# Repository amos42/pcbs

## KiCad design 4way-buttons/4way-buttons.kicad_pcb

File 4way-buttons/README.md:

# Monitor Control Board

회로도

PCB 이미지

샘플 이미지

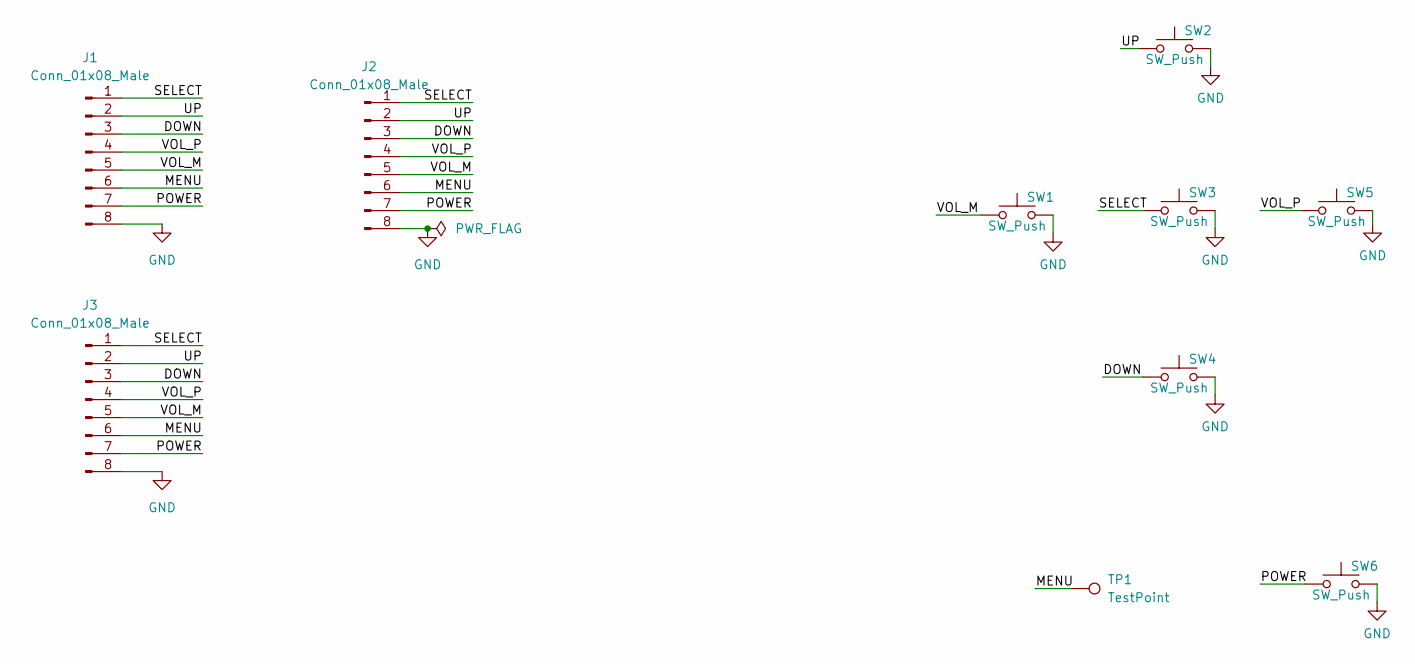
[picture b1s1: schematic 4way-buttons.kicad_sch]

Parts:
J1: Conn_01x08_Male; JST_GH_SM08B-GHS-TB_1x08-1MP_P1.25mm_Horizontal
J2: Conn_01x08_Male; PinHeader_1x08_P2.54mm_Vertical
J3: Conn_01x08_Male; JST_PH_S8B-PH-K_1x08_P2.00mm_Horizontal
SW1, SW2, SW3, SW4, SW5: SW_Push; SW_PUSH-12mm
SW6: SW_Push; SW_PUSH_6mm
TP1: TestPoint; TestPoint_Pad_D2.0mm

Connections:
/DOWN: J1.3, J2.3, J3.3, SW4.1
/MENU: J1.6, J2.6, J3.6, TP1.1
/POWER: J1.7, J2.7, J3.7, SW6.1
/SELECT: J1.1, J2.1, J3.1, SW3.1
/UP: J1.2, J2.2, J3.2, SW2.1
/VOL_M: J1.5, J2.5, J3.5, SW1.1
/VOL_P: J1.4, J2.4, J3.4, SW5.1
GND: J1.8, J2.8, J3.8, SW1.2, SW2.2, SW3.2, SW4.2, SW5.2, SW6.2

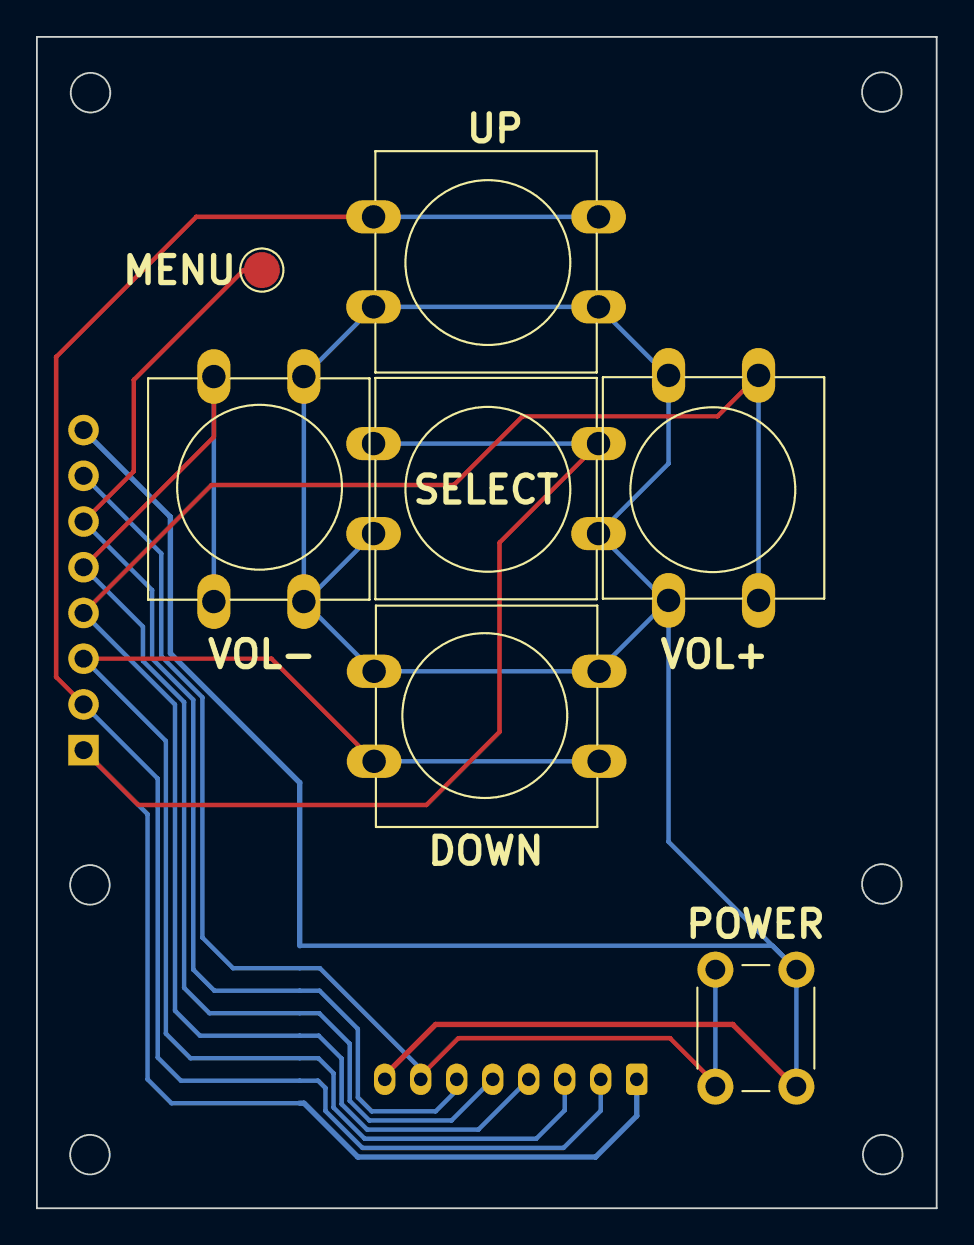
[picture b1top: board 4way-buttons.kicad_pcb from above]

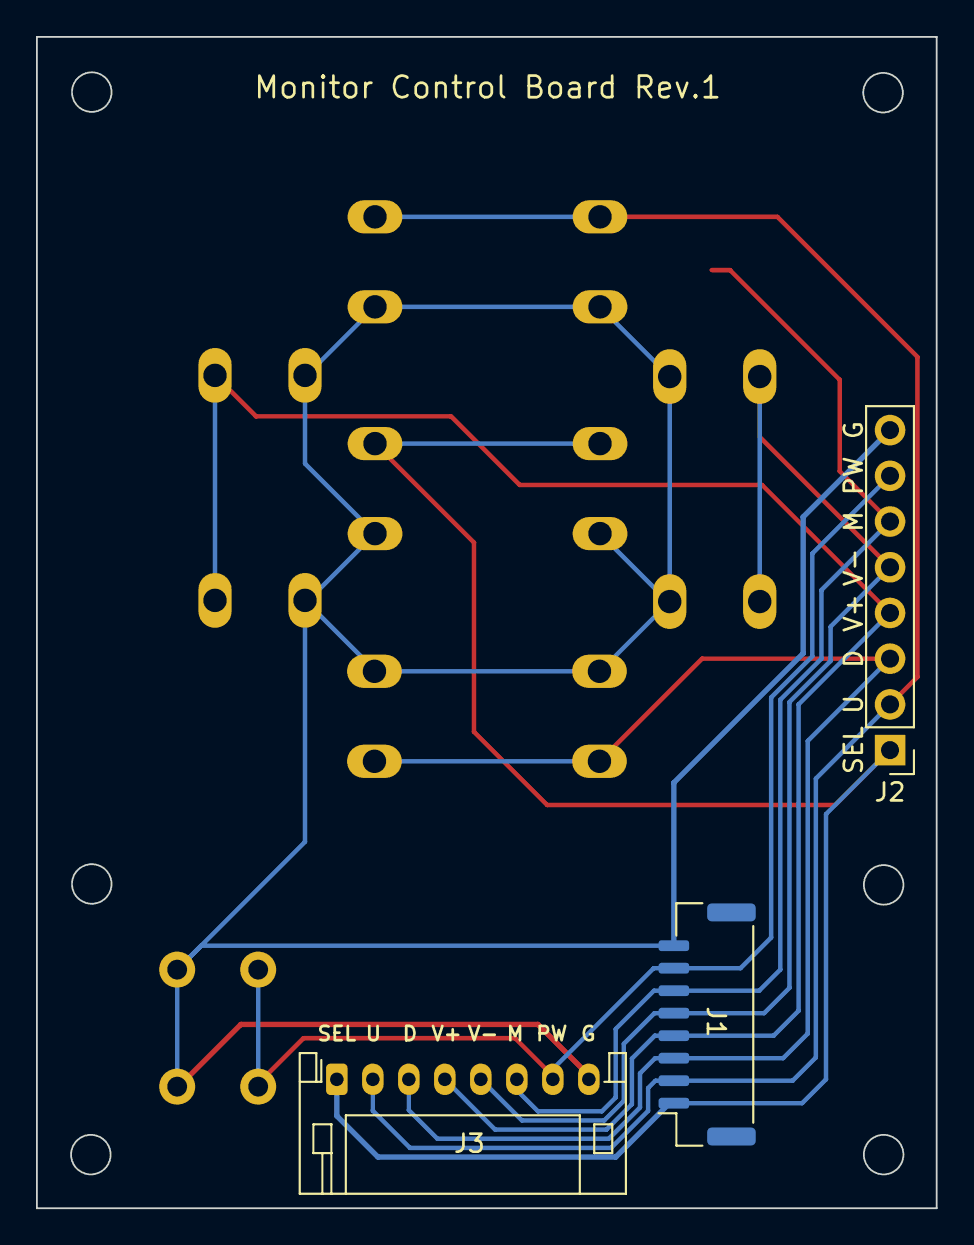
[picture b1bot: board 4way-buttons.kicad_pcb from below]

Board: 2 copper layers, 50.0 x 65.1 mm, 10 parts (3 on the bottom side), 8 nets.

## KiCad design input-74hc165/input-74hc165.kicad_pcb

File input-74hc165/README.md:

# 74HC165 입력 보드

회로도

PCB 이미지 앞면

PCB 이미지 뒷면

샘플 이미지

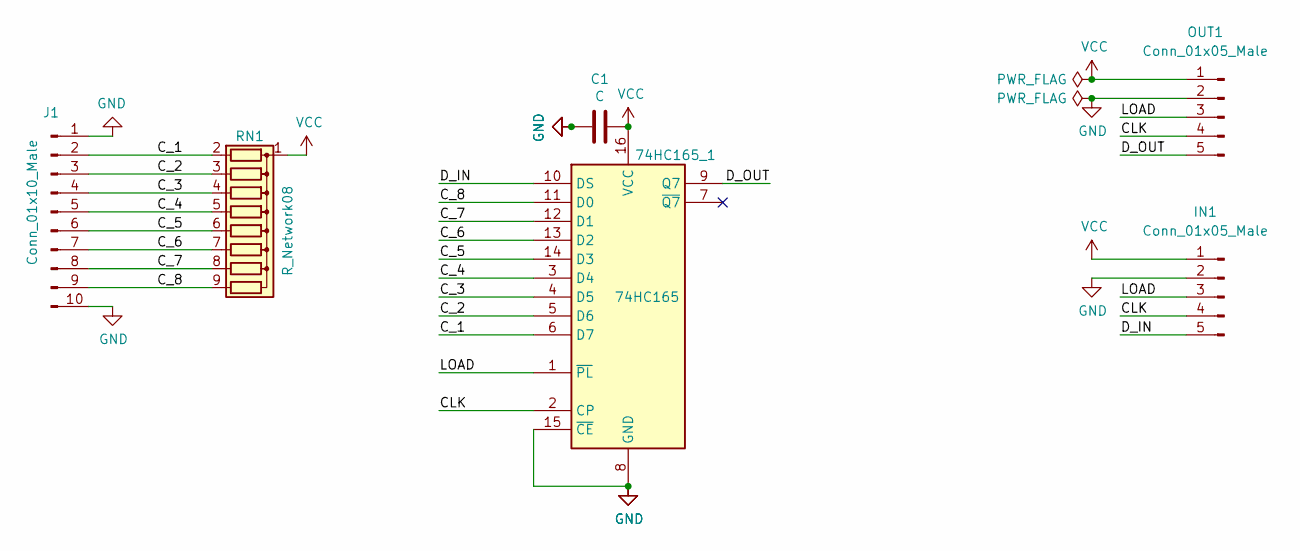
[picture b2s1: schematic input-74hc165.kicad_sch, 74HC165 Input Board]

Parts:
74HC165_1: 74HC165; DIP-16_W7.62mm
C1: C; C_Disc_D4.3mm_W1.9mm_P5.00mm
IN1: Conn_01x05_Male; PinHeader_1x05_P2.54mm_Vertical
J1: Conn_01x10_Male; PinHeader_1x10_P2.54mm_Vertical
OUT1: Conn_01x05_Male; PinHeader_1x05_P2.54mm_Vertical
RN1: R_Network08; R_Array_SIP9

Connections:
/CLK: 74HC165_1.2 (CP), IN1.4, OUT1.4
/C_1: 74HC165_1.6 (D7), J1.2, RN1.2 (R1)
/C_2: 74HC165_1.5 (D6), J1.3, RN1.3 (R2)
/C_3: 74HC165_1.4 (D5), J1.4, RN1.4 (R3)
/C_4: 74HC165_1.3 (D4), J1.5, RN1.5 (R4)
/C_5: 74HC165_1.14 (D3), J1.6, RN1.6 (R5)
/C_6: 74HC165_1.13 (D2), J1.7, RN1.7 (R6)
/C_7: 74HC165_1.12 (D1), J1.8, RN1.8 (R7)
/C_8: 74HC165_1.11 (D0), J1.9, RN1.9 (R8)
/D_IN: 74HC165_1.10 (DS), IN1.5
/D_OUT: 74HC165_1.9 (Q7), OUT1.5
/LOAD: 74HC165_1.1 (~PL), IN1.3, OUT1.3
GND: 74HC165_1.8 (GND), 74HC165_1.15 (~CE), C1.2, IN1.2, J1.1, J1.10, OUT1.2
VCC: 74HC165_1.16 (VCC), C1.1, IN1.1, OUT1.1, RN1.1 (common)

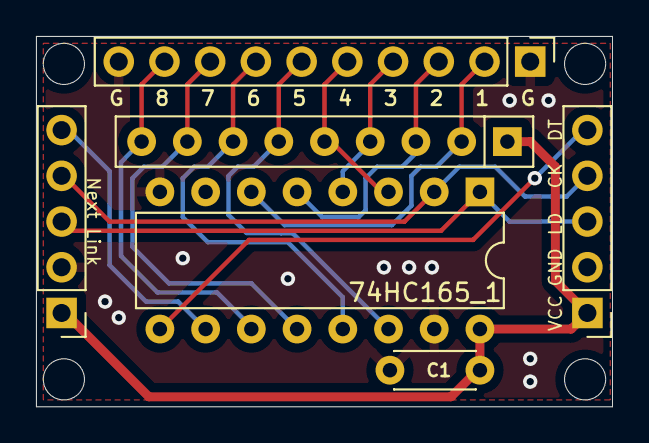
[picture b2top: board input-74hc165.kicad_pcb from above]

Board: 2 copper layers, 32.0 x 20.6 mm, 6 parts (0 on the bottom side), 14 nets.

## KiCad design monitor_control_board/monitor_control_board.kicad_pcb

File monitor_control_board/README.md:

# Monitor OSD Control Board

회로도

PCB 이미지

샘플 이미지

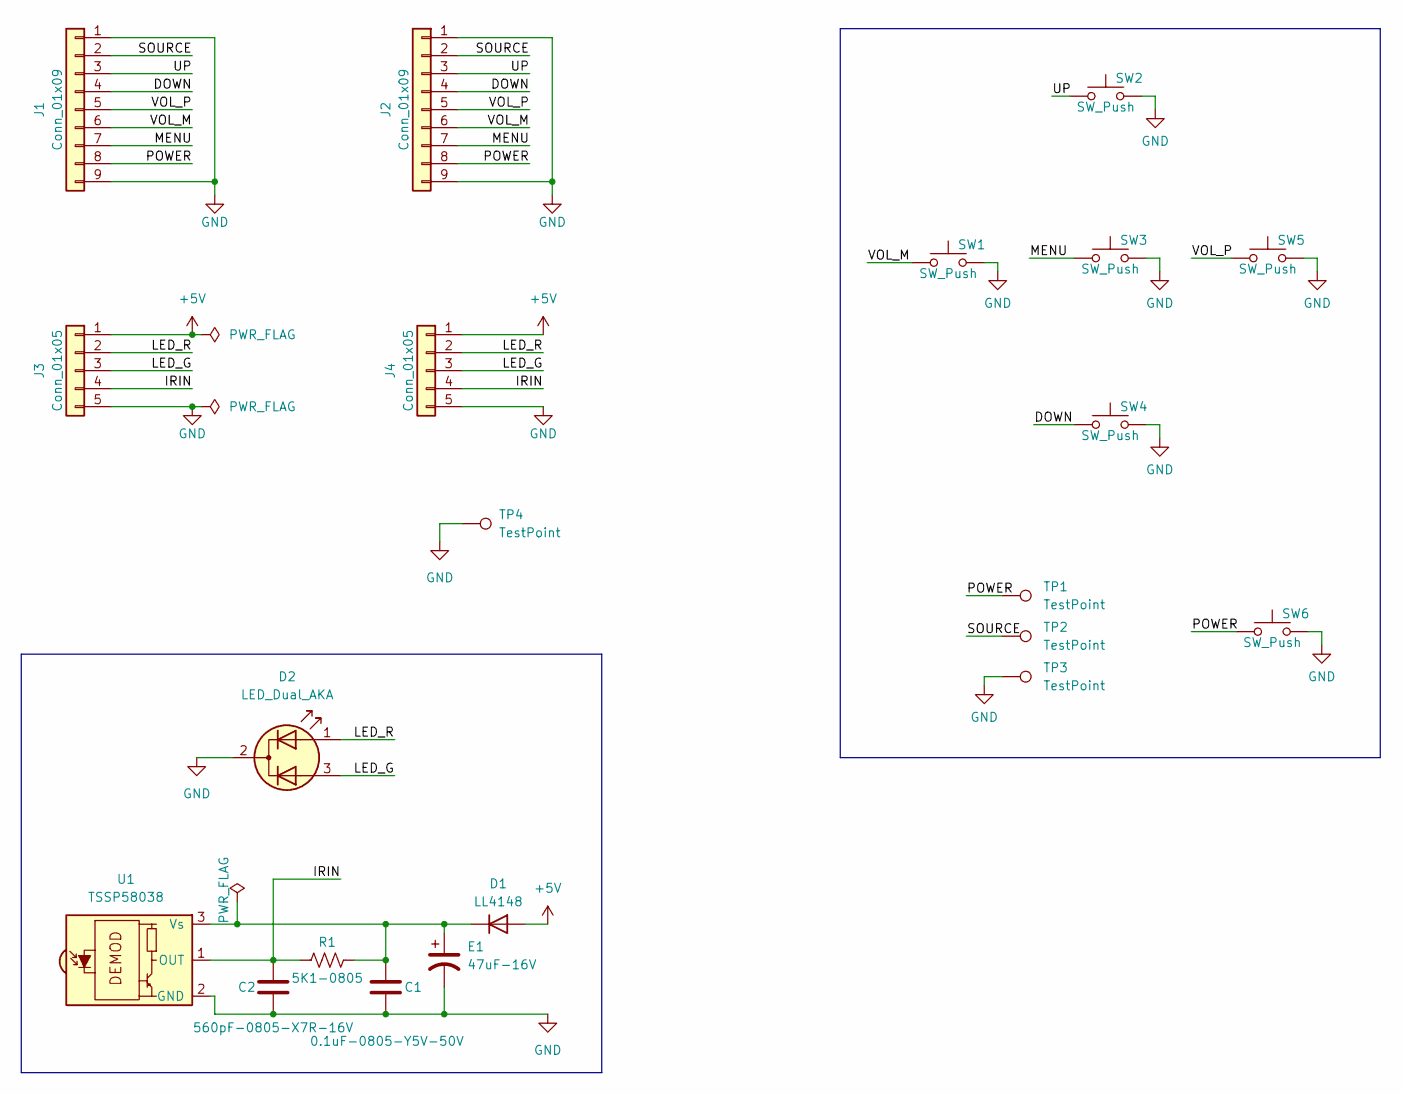
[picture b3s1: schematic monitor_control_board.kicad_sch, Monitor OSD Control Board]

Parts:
C1: 0.1uF-0805-Y5V-50V; C_0805_2012Metric_Pad1.18x1.45mm_HandSolder
C2: 560pF-0805-X7R-16V; C_0805_2012Metric_Pad1.18x1.45mm_HandSolder
D1: LL4148; D_MiniMELF
D2: LED_Dual_AKA; LED_D3.0mm-3
E1: 47uF-16V; CP_Elec_4x5.4
J1: Conn_01x09; PinHeader_1x09_P2.00mm_Vertical
J2: Conn_01x09; PinHeader_1x09_P2.54mm_Vertical
J3: Conn_01x05; PinHeader_1x05_P2.00mm_Vertical
J4: Conn_01x05; PinHeader_1x05_P2.54mm_Vertical
R1: 5K1-0805; R_0805_2012Metric_Pad1.20x1.40mm_HandSolder
SW1, SW2, SW3, SW4, SW5: SW_Push; SW_PUSH-12mm_Complex
SW6: SW_Push; SW_PUSH_6mm
TP1, TP2, TP3: TestPoint; TestPoint_THTPad_D1.5mm_Drill0.7mm
TP4: TestPoint; TestPoint_THTPad_D2.0mm_Drill1.0mm
U1: TSSP58038; Vishay_MINICAST-3Pin

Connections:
+5V: D1.2 (A), J3.1, J4.1
/DOWN: J1.4, J2.4, SW4.1
/IRIN: C2.1, J3.4, J4.4, R1.1, U1.1 (OUT)
/LED_G: D2.3 (A2), J3.3, J4.3
/LED_R: D2.1 (A1), J3.2, J4.2
/MENU: J1.7, J2.7, SW3.1
/POWER: J1.8, J2.8, SW6.1, TP1.1
/SOURCE: J1.2, J2.2, TP2.1
/UP: J1.3, J2.3, SW2.1
/VOL_M: J1.6, J2.6, SW1.1
/VOL_P: J1.5, J2.5, SW5.1
GND: C1.2, C2.2, D2.2 (K), E1.2, J1.1, J1.9, J2.1, J2.9, J3.5, J4.5, SW1.2, SW2.2, SW3.2, SW4.2, SW5.2, SW6.2, TP3.1, TP4.1, U1.2 (GND)
unnamed: C1.1, D1.1 (K), E1.1, R1.2, U1.3 (Vs)

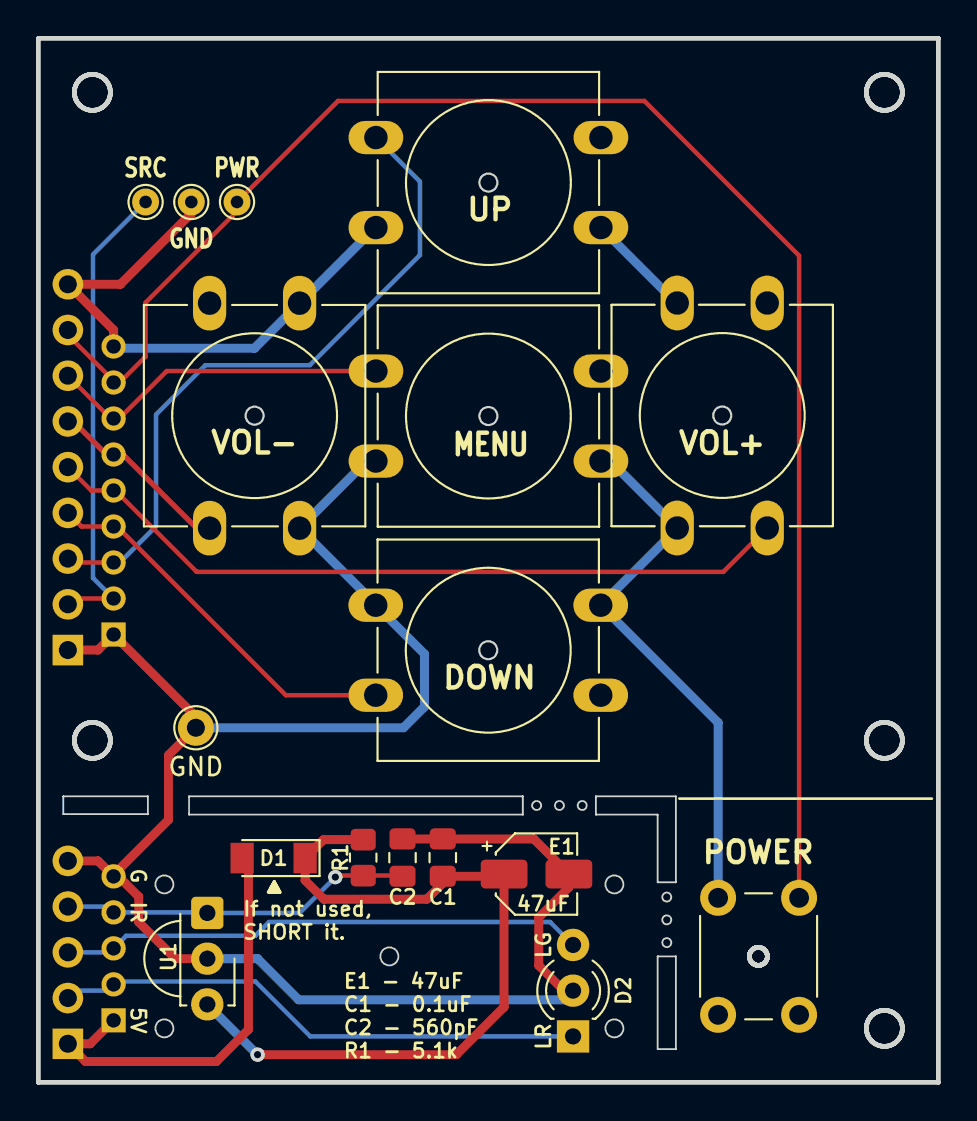
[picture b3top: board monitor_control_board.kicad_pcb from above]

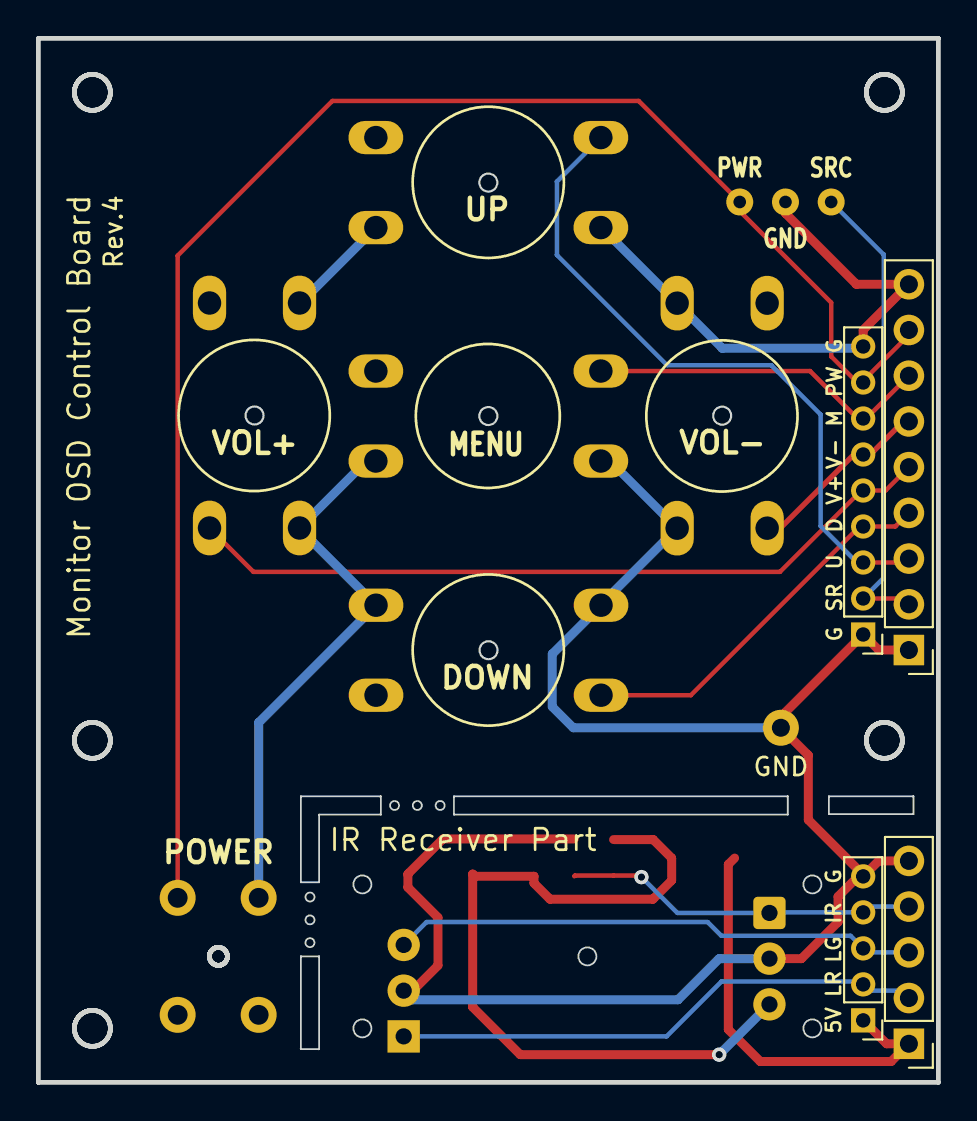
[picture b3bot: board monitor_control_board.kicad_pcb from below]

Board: 2 copper layers, 50.0 x 58.0 mm, 21 parts (4 on the bottom side), 13 nets.

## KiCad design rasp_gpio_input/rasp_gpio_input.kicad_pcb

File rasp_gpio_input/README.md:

# Raspberry Pie GPIO 입력 모듈

GPIO 보호 기능을 갖는 입력 모듈

---

## 회로도

## PCB

## BOM

| Designator | Package | Quantity | Designation |
|------------|---------|----------|-------------|
| R1~R13 | R_0805_2012Metric | 13 | 6.8K

## PCB 이미지

### 앞면

### 뒷면

## 샘플 이미지

## 점퍼 세팅

커넥터 중 J3는 일부 핀을 점퍼 세팅으로 변경이 가능하다.

* R* - 1-2 끊고 2-3 쇼트시, J3의 Right 핀이 GND로 쇼트
* ST* - 1-2 끊고 2-3 쇼트시, J3의 Start 핀이 GND로 쇼트
* SL* - 1-2 끊고 2-3 쇼트시, J3의 Select 핀이 GND로 쇼트
* HK* - 1-2 끊고 2-3 쇼트시, J3의 HotKey 핀이 GND로 쇼트

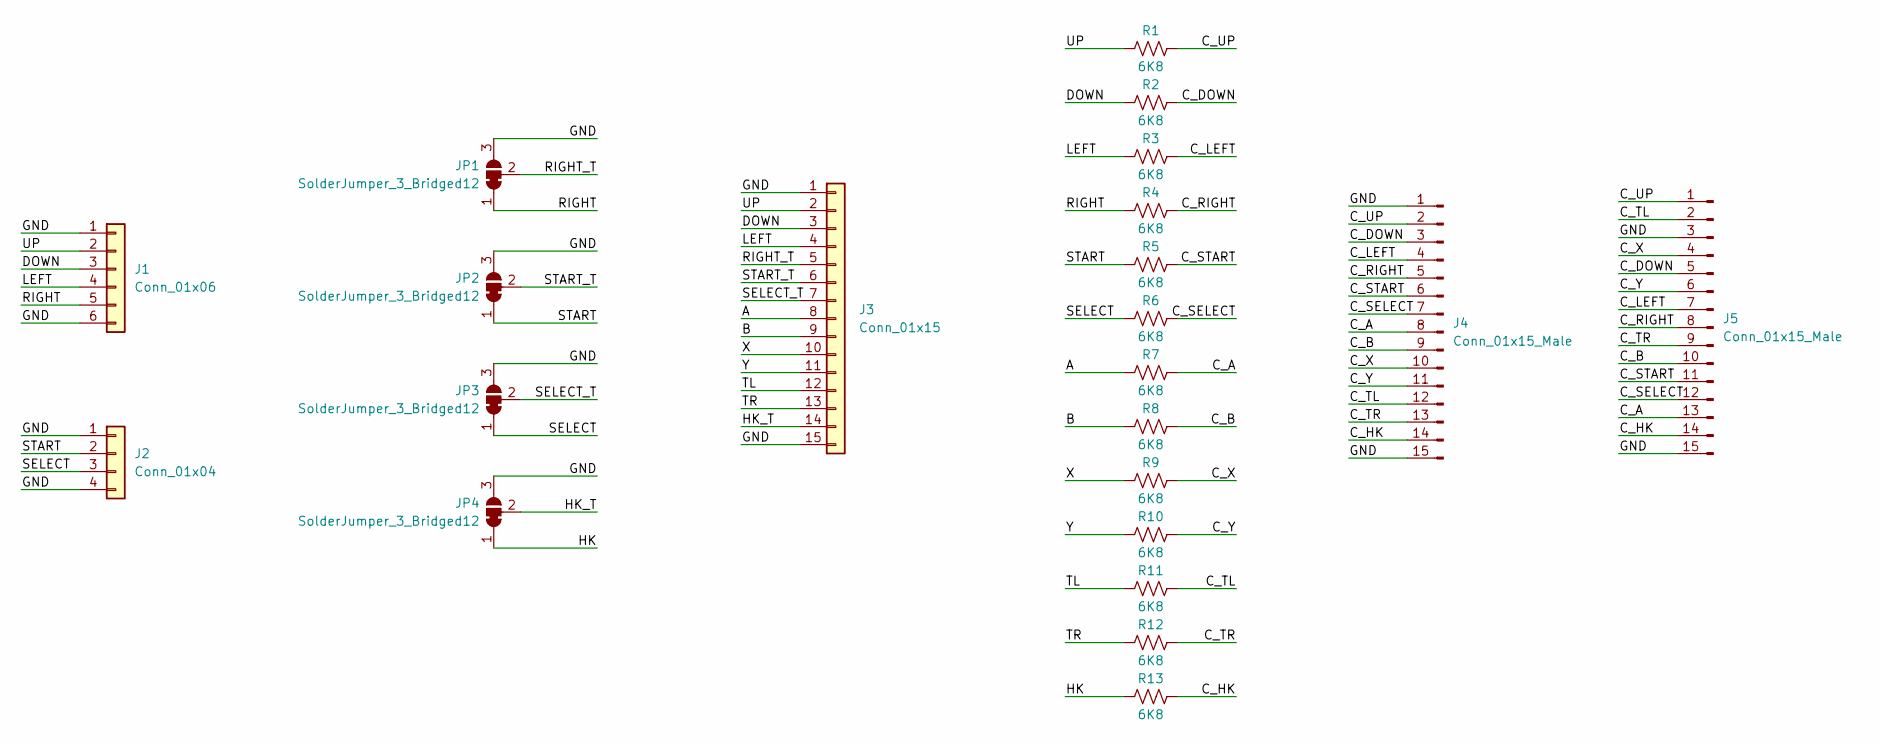
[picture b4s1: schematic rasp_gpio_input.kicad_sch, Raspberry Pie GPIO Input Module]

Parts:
J1: Conn_01x06; Molex_PicoBlade_53047-0610_1x06_P1.25mm_Vertical
J2: Conn_01x04; Molex_PicoBlade_53047-0410_1x04_P1.25mm_Vertical
J3: Conn_01x15; Molex_PicoBlade_53047-1510_1x15_P1.25mm_Vertical
J4, J5: Conn_01x15_Male; PinHeader_1x15_P2.54mm_Vertical
JP1, JP2, JP3, JP4: SolderJumper_3_Bridged12; SolderJumper-3_P1.3mm_Bridged12_Pad1.0x1.5mm
R1, R2, R3, R4, R5, R6, R7, R8, R9, R10, R11, R12, R13: 6K8; R_0805_2012Metric_Pad1.20x1.40mm_HandSolder

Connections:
/A: J3.8, R7.1
/B: J3.9, R8.1
/C_A: J4.8, J5.13, R7.2
/C_B: J4.9, J5.10, R8.2
/C_DOWN: J4.3, J5.5, R2.2
/C_HK: J4.14, J5.14, R13.2
/C_LEFT: J4.4, J5.7, R3.2
/C_RIGHT: J4.5, J5.8, R4.2
/C_SELECT: J4.7, J5.12, R6.2
/C_START: J4.6, J5.11, R5.2
/C_TL: J4.12, J5.2, R11.2
/C_TR: J4.13, J5.9, R12.2
/C_UP: J4.2, J5.1, R1.2
/C_X: J4.10, J5.4, R9.2
/C_Y: J4.11, J5.6, R10.2
/DOWN: J1.3, J3.3, R2.1
/GND: J1.1, J1.6, J2.1, J2.4, J3.1, J3.15, J4.1, J4.15, J5.3, J5.15, JP1.3 (B), JP2.3 (B), JP3.3 (B), JP4.3 (B)
/HK: JP4.1 (A), R13.1
/HK_T: J3.14, JP4.2 (C)
/LEFT: J1.4, J3.4, R3.1
/RIGHT: J1.5, JP1.1 (A), R4.1
/RIGHT_T: J3.5, JP1.2 (C)
/SELECT: J2.3, JP3.1 (A), R6.1
/SELECT_T: J3.7, JP3.2 (C)
/START: J2.2, JP2.1 (A), R5.1
/START_T: J3.6, JP2.2 (C)
/TL: J3.12, R11.1
/TR: J3.13, R12.1
/UP: J1.2, J3.2, R1.1
/X: J3.10, R9.1
/Y: J3.11, R10.1

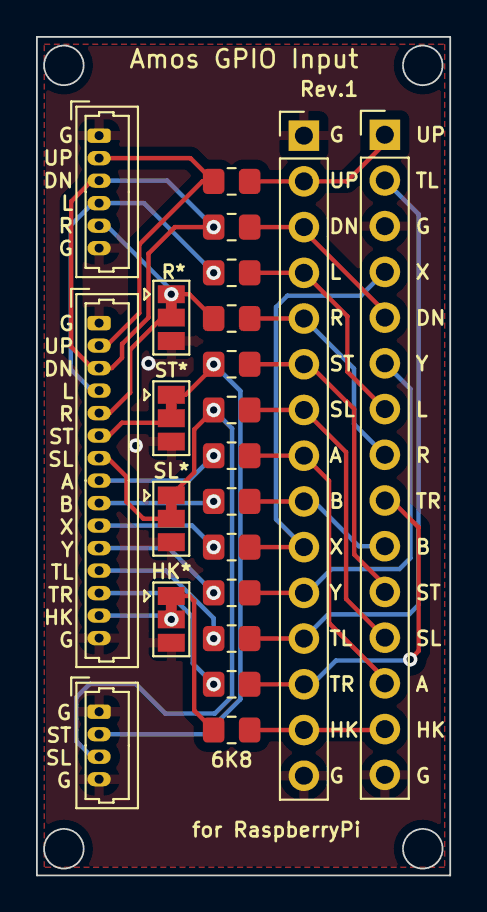
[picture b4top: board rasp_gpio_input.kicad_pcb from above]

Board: 2 copper layers, 23.0 x 46.6 mm, 22 parts (0 on the bottom side), 31 nets.

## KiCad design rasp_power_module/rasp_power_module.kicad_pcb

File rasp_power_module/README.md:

# Raspberry Pie Power Module

Safety-shutdown 기능을 포함한 라즈베리파이의 전원 모듈

---

## 회로도

## PCB

## BOM

| Designator | Package | Quantity | Designation |
|------------|---------|----------|-------------|
| K1 | Relay_SPDT_Omron_G5V-1 | 1 | G5V-1
| K2 | Relay_SPDT_Finder_36.11 | 1 | FINDER-36.11
| R1 | R_0805_2012Metric | 1 | 1K
| R2 | R_0805_2012Metric | 1 | 10K
| R3 | R_0805_2012Metric | 1 | 100K
| R4 | R_0805_2012Metric | 1 | 30K 
| R5 | R_0805_2012Metric | 1 | 4K7
| D1 | D_MiniMELF | 1 | LL4148
| D2 | D_SMC-RM10_Universal_Handsoldering | 1 | 1N4007
| D3 | LED_0805_2012Metric | 1 | LED
| Q1 | SOT-23 | 1 | S8050 J3Y
| J2 | JST_XH_B5B-XH-A_1x05_P2.50mm_Vertical | 1 | Conn_01x05
| J3 | PinHeader_1x02_P2.54mm_Vertical | 1 | Conn_01x02
| JP1,JP2 | PinHeader_2x01_P2.54mm_Vertical	| 2 | Jumper_2_Open
| J7,J9,J8 | JST_XH_B2B-XH-A_1x02_P2.50mm_Vertical | 3 | Conn_01x02

## PCB 이미지

### 앞면

### 뒷면

## 샘플 이미지

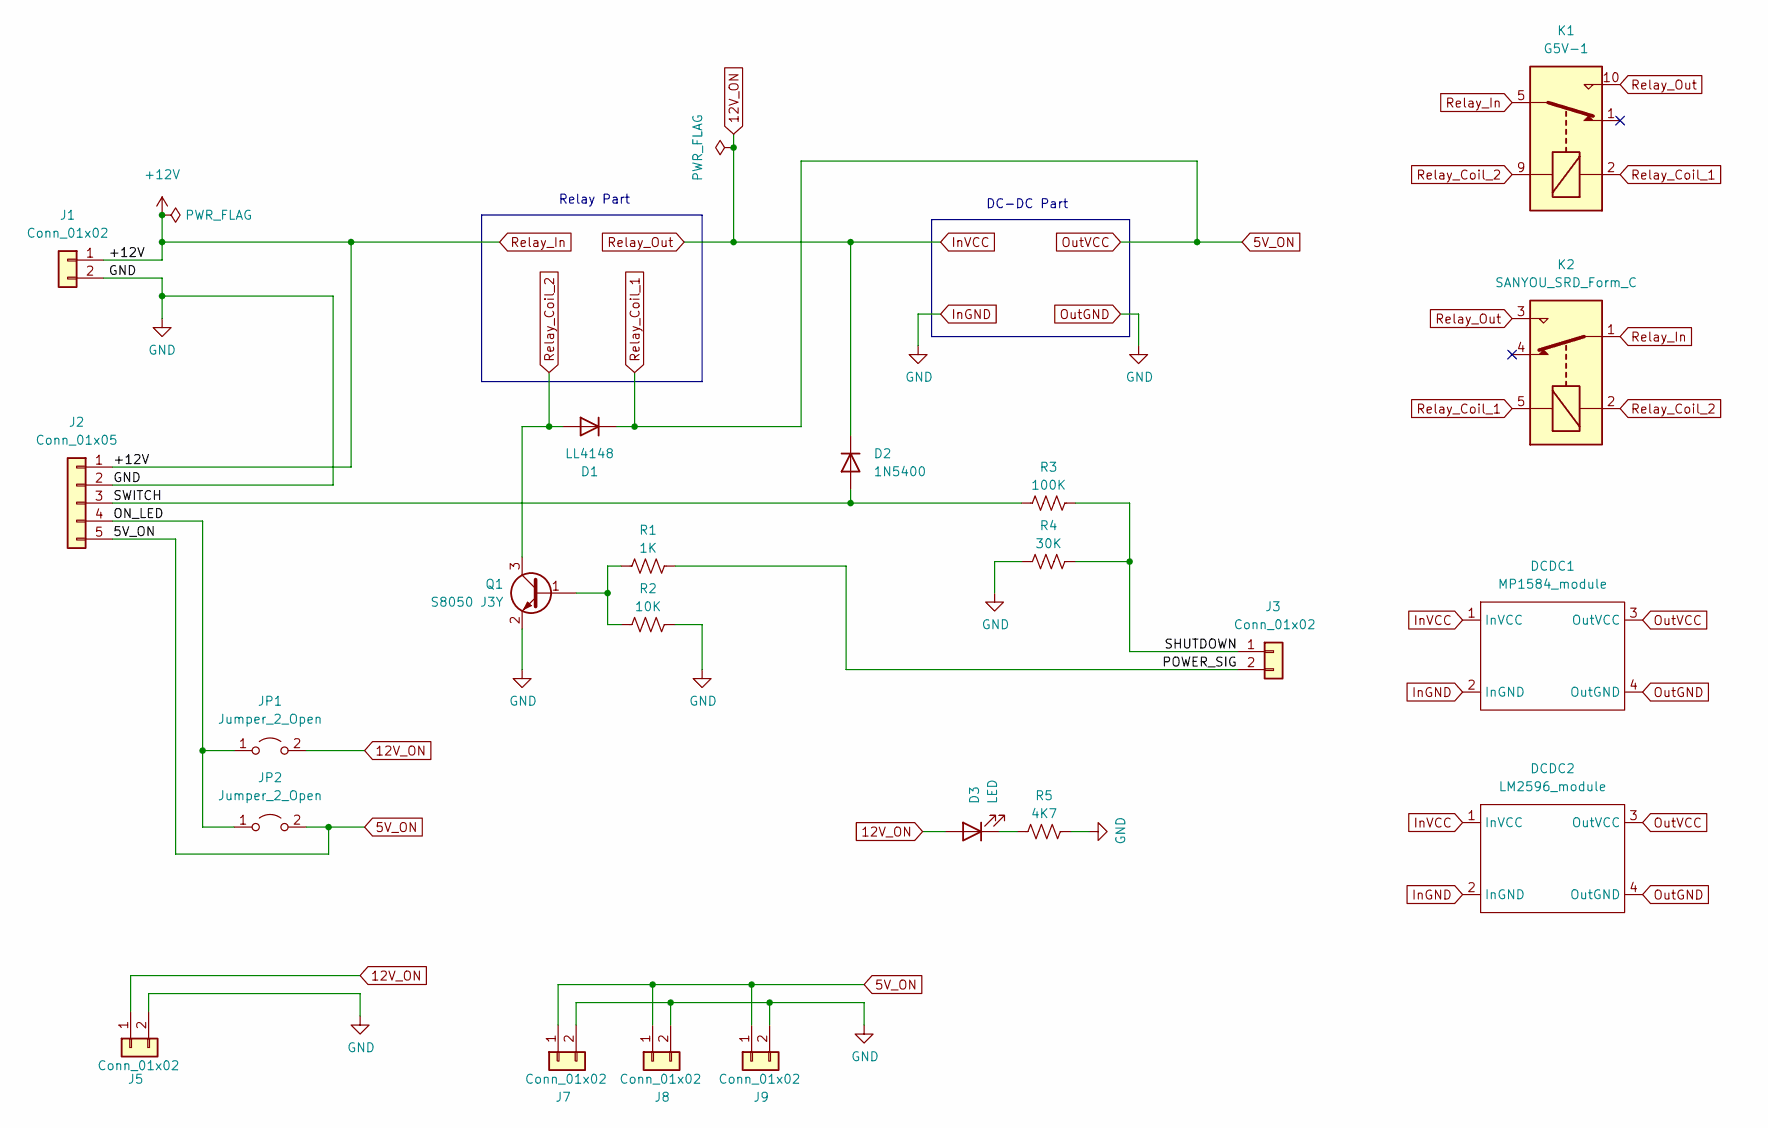
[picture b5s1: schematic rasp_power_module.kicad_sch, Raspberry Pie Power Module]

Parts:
D1: LL4148; D_MiniMELF
D2: 1N5400; D_DO-201AD_P15.24mm_Horizontal
D3: LED; LED_0805_2012Metric
DCDC1: MP1584_module; MP1584_dcdc_module
DCDC2: LM2596_module; LM2596_dcdc_module
J1: Conn_01x02; SolderWire-1.5sqmm_1x02_P7.8mm_D1.7mm_OD3.9mm
J2: Conn_01x05; JST_XH_B5B-XH-A_1x05_P2.50mm_Vertical
J3: Conn_01x02; PinHeader_1x02_P2.54mm_Vertical
J5: Conn_01x02; SolderWire-1.5sqmm_1x02_P6mm_D1.7mm_OD3mm
J7, J8, J9: Conn_01x02; JST_XH_B2B-XH-A_1x02_P2.50mm_Vertical
JP1, JP2: Jumper_2_Open; PinHeader_2x01_P2.54mm_Vertical
K1: G5V-1; Relay_SPDT_Omron_G5V-1
K2: SANYOU_SRD_Form_C; Relay_SPDT_SANYOU_SRD_Series_Form_C
Q1: S8050 J3Y; SOT-23
R1: 1K; R_0805_2012Metric
R2: 10K; R_0805_2012Metric
R3: 100K; R_0805_2012Metric
R4: 30K; R_0805_2012Metric
R5: 4K7; R_0805_2012Metric

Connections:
5V_ON: D1.1 (K), DCDC1.3 (OutVCC), DCDC2.3 (OutVCC), J2.5, J7.1, J8.1, J9.1, JP2.2 (B), K1.2, K2.5
12V_ON: D2.1 (K), D3.2 (A), DCDC1.1 (InVCC), DCDC2.1 (InVCC), J5.1, JP1.2 (B), K1.10, K2.3
/ON_LED: J2.4, JP1.1 (A), JP2.1 (A)
/POWER_SIG: J3.2, R1.1
/SHUTDOWN: J3.1, R3.2, R4.2
/SWITCH: D2.2 (A), J2.3, R3.1
InGND: DCDC1.2 (InGND), DCDC1.4 (OutGND), DCDC2.2 (InGND), DCDC2.4 (OutGND), J1.2, J2.2, J5.2, J7.2, J8.2, J9.2, Q1.2 (E), R2.1, R4.1, R5.1
unnamed: D3.1 (K), R5.2
unnamed: Q1.1 (B), R1.2, R2.2
Relay_Coil_2: D1.2 (A), K1.9, K2.2, Q1.3 (C)
Relay_In: J1.1, J2.1, K1.5, K1.6, K2.1

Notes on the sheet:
Relay Part
DC-DC Part

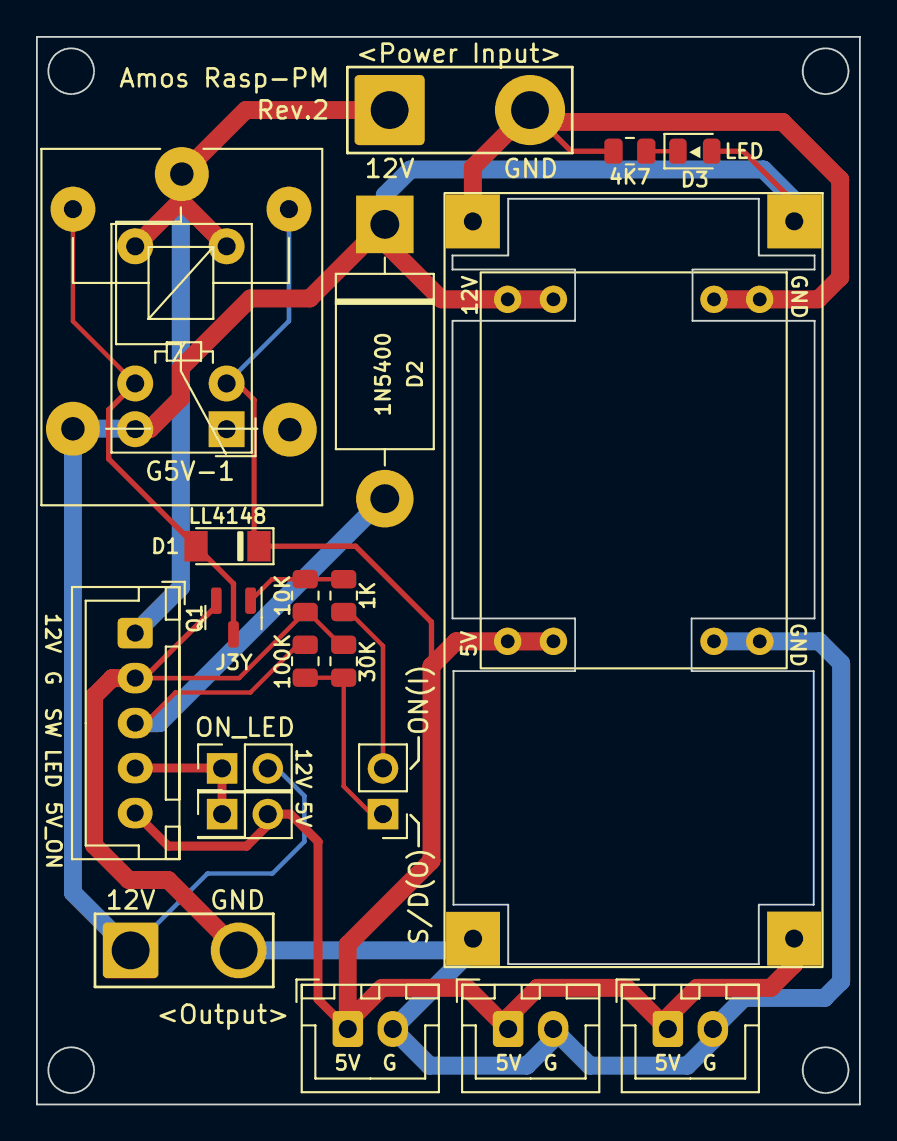
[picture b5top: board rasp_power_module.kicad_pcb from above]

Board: 2 copper layers, 45.7 x 59.3 mm, 22 parts (0 on the bottom side), 11 nets.

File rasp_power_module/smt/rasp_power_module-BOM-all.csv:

"Id";"Designator";"Package";"Quantity";"Designation";"Supplier and ref";
1;"D2";"D_DO-201AD_P15.24mm_Horizontal";1;"1N5400";;;
2;"DCDC1";"MP1584_dcdc_module";1;"MP1584_module";;;
3;"R1";"R_0805_2012Metric";1;"1K";;;
4;"DCDC2";"LM2596_dcdc_module";1;"LM2596_module";;;
5;"JP1,JP2";"PinHeader_2x01_P2.54mm_Vertical";2;"Jumper_2_Open";;;
6;"R4";"R_0805_2012Metric";1;"30K";;;
7;"J5";"SolderWire-1.5sqmm_1x02_P6mm_D1.7mm_OD3mm";1;"Conn_01x02";;;
8;"R2";"R_0805_2012Metric";1;"10K";;;
9;"J3";"PinHeader_1x02_P2.54mm_Vertical";1;"Conn_01x02";;;
10;"K1";"Relay_SPDT_Omron_G5V-1";1;"G5V-1";;;
11;"J7,J9,J8";"JST_XH_B2B-XH-A_1x02_P2.50mm_Vertical";3;"Conn_01x02";;;
12;"R5";"R_0805_2012Metric";1;"4K7";;;
13;"D3";"LED_0805_2012Metric";1;"LED";;;
14;"J1";"SolderWire-1.5sqmm_1x02_P7.8mm_D1.7mm_OD3.9mm";1;"Conn_01x02";;;
15;"Q1";"SOT-23";1;"S8050 J3Y";;;
16;"K2";"Relay_SPDT_SANYOU_SRD_Series_Form_C";1;"SANYOU_SRD_Form_C";;;
17;"D1";"D_MiniMELF";1;"LL4148";;;
18;"J2";"JST_XH_B5B-XH-A_1x05_P2.50mm_Vertical";1;"Conn_01x05";;;
19;"R3";"R_0805_2012Metric";1;"100K";;;
